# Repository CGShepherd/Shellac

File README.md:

# Project Shellac

Shellac is a controlled 78 rpm replay preamplifier design. `develop` is the working engineering authority; a tagged `main` release becomes production authority only after qualification and reproducibility gates close.

## Current authority

Read these first:

1. `config/decisions/current_decision_index.yaml`
2. `config/decisions/document_authority.yaml`
3. `docs/knowledge/DESIGN_PACK_INDEX.md`
4. current `generator/`, BOM and tests
5. current pre-SPICE assurance records in `docs/design_pack/`

Historical records are provenance and do not override later current authority.

## Live implementation versus selected-next architecture

- DR-037 complete RIAA: implemented.
- DR-038/SCH101: AE-071A gain programming remains live at approximately 14/18/22 dB; AE-075B selects LT5400BIMS8E-7#PBF and bonds EP9 to quiet 0VA. AE-076C selects two local per-channel passive cartridge-personality cards using SLW-102-01-G-D main sockets and TSW-102-07-G-D card headers; no card=BASE, with matched +47/+100 pF L/R service pairs. AE-076E-A qualifies the exact interface primitive; AE-076E-B implements H120/H220 in both generator and native PCB, removing the legacy ganged hardware. Three corrected project-local solid models pass KiCad STEP export; exact Samtec mated geometry remains open. RUN10 complete-stage tolerance/CMRR, personality-interface parasitics/matching, gain-shunt physical verification and bench qualification remain open.
- DR-039/SCH107: AE-074 migrates the AE-067 branch-local topology into the live generator: the retained 1 uF / 330 kOhm network exists only in each DIRECT/BYPASS branch, while the existing SCH107 high-pass branch provides intrinsic DC blocking. Native-PCB F8/net reconciliation is closed by AE-074; RUN09, RUN10, RUN12 and bench correlation remain open.
- SCH108/output interface: AE-075G implements exact Molex 5055780221 two-circuit PCB headers H801/H802 for the short rear-panel balanced-output looms, validates HOT/COLD native pad mapping with no 0VA conductor, corrects THAT1646 source semantics to 25 Ohm per leg / 50 Ohm differential, and passes the application-specific PRE90 2 kOhm load discriminator. H801/H802 XY remains provisional pending manual placement reconciliation; RUN06 load/cable stability and dynamic-THD bench gates remain open.
- AE-041 A1 + AE-075C hardware + AE-076B controls: exact NKK/C&K hardware remains frozen. AE-076B supersedes the AE-075D/E/F four-local-control-board/carrier-era ownership architecture with one main audio PCB carrying all seven controls directly; the upper cover, main PCB and controls form one removable service module. Six PCB-to-upper-cover supports are selected in principle, but exact support XY/Z, the C&K fit at the NKK-constrained control plane, control XY, footprints/courtyards, panel apertures and RUN10 parasitic acceptance remain B03-open. SR-040/AE-071B MH1-MH4 native geometry is retained only as interim physical CAD pending the AE-076B2 MCAD/digital-mock-up migration; no control inter-board harnesses are selected.
- SW905 mute: mechanical DPDT signal/0VA selection immediately before the THAT1646 drivers. No relay/timer/comparator architecture.

Do not change live circuitry merely to make it resemble a selected-next record. Migration requires a controlled qualification and implementation step.

## Power and grounding

AE-076A establishes +17.0 V / 0VA / -17.0 V as current Shellac regulated-rail authority and migrates the live generator, current simulation contract, commissioning expectations and native PCB rail identities together. Historical +/-18 V assurance evidence remains immutable provenance. AE-073's target-17 PSU discriminator remains supporting model evidence only: powered set-point, dropout, ripple, startup and thermal qualification remain open under RUN13/RUN14 and bench work. The selected direct 0VA-to-chassis population remains R909 = 0 Ohm fitted, with C909, D901 and D902 DNP. Shellac and Phoenix are independent designs.

## Simulation

AE-053 defines the LTspice/Python simulation architecture. AE-054 through AE-058 establish implemented toolchain and numerical-correlation evidence. The integrated full-system campaign remains governed by AE-048 and AE-050 with AE-049 retained as the historical numerical-acceptance basis; AE-076A establishes the current nominal +17 V / 0VA / -17 V rail condition and targeted rail/headroom evidence. AE-076D publishes the current qualification delta that maps the retained method to Grado Prestige 78C and BASE/+47/+100 differential personality states without relaxing criteria or claiming RUN08-RUN14 execution. Analytical Python is an independent live-state regression/correlation aid, not final integrated analogue authority.

## Basic validation

    python -m pytest -q
    python tools/audit_current_decision_index.py
    git diff --check

This repository is not yet a manufacturing baseline.

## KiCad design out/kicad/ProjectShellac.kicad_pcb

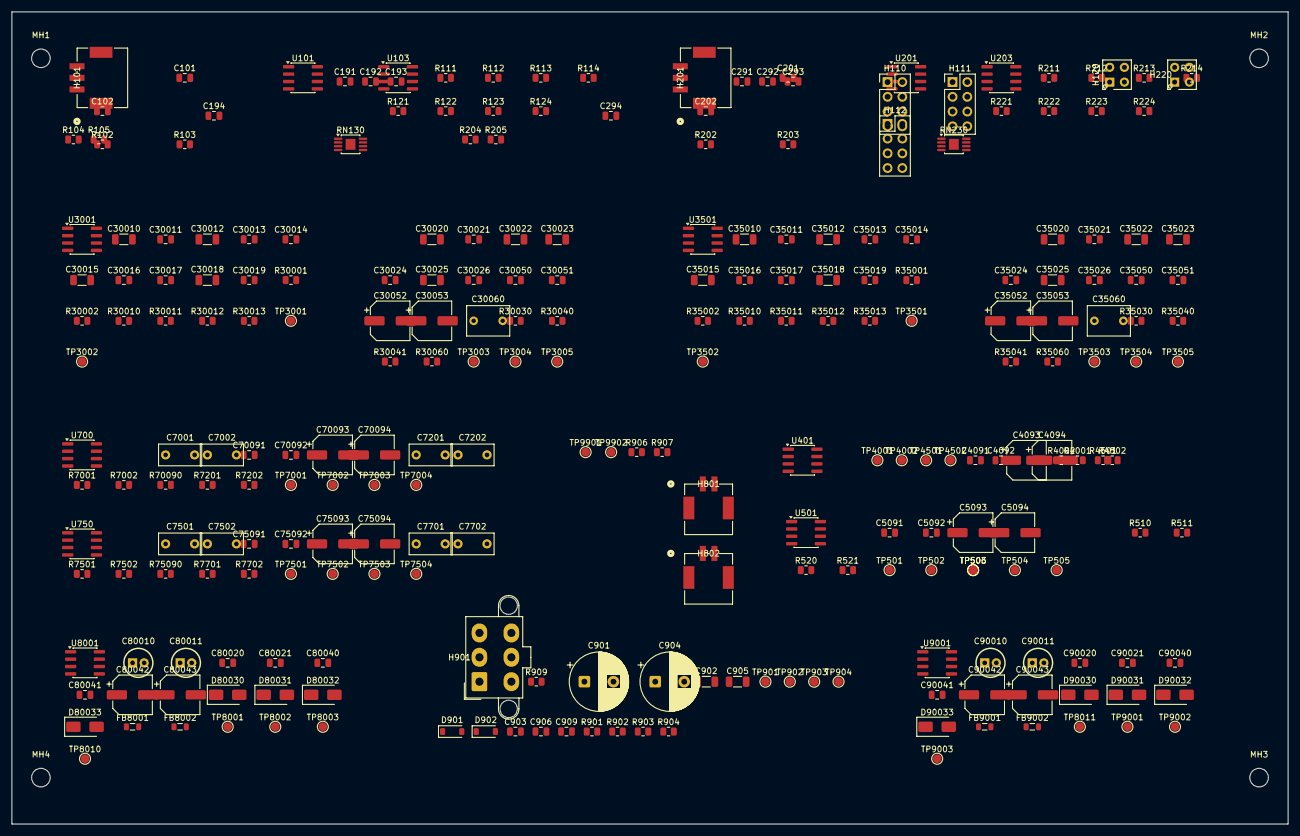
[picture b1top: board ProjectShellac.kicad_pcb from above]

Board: 4 copper layers, 220.0 x 140.0 mm, 256 parts (0 on the bottom side), 110 nets, no tracks yet.

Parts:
C101, C102, C201, C202: 47p; C_0805_2012Metric
C191, C192, C193, C194, C291, C292, C293, C294, C903, C906, C909, C4091, C4092, C5091, C5092, C30050, C30051, C35050, C35051, C70091, C70092, C75091, C75092, C80040, C80041, C90040, C90041: 100n; C_0805_2012Metric
C901, C904: 470u; CP_Radial_D10.0mm_P5.00mm
C902, C905: 1u; C_1206_3216Metric
C4093, C4094, C5093, C5094, C30052, C30053, C35052, C35053, C70093, C70094, C75093, C75094, C80042, C80043, C90042, C90043: 10u; CP_Elec_6.3x5.8
C7001, C7002, C7201, C7202, C7501, C7502, C7701, C7702: 470n; C_Rect_L7.2mm_W3.5mm_P5.00mm_FKS2_FKP2_MKS2_MKP2
C30010, C30012, C30015, C35010, C35012, C35015: 68n; C_1206_3216Metric
C30011, C35011: 5.6n; C_0805_2012Metric
C30013, C35013: 9.1n; C_0805_2012Metric
C30014, C35014: 560p; C_0805_2012Metric
C30016, C35016: 10n; C_0805_2012Metric
C30017, C35017: 470p; C_0805_2012Metric
C30018, C35018: 27n; C_1206_3216Metric
C30019, C35019: 2.4n; C_0805_2012Metric
C30020, C35020: 120n; C_1206_3216Metric
C30021, C35021: 12n; C_0805_2012Metric
C30022, C35022: 100n; C_1206_3216Metric
C30023, C35023: 56n; C_1206_3216Metric
C30024, C35024: 6.2n; C_0805_2012Metric
C30025, C35025: 33n; C_1206_3216Metric
C30026, C35026: 3.6n; C_0805_2012Metric
C30060, C35060: 1u; C_Rect_L7.2mm_W5.0mm_P5.00mm
C80010, C80011, C90010, C90011: 10u NP; Panasonic_ECEA1VN100U_D5.0mm_H11.0mm_P2.00mm
C80020, C80021, C90020, C90021: 100p; C_0805_2012Metric
D901, D902: DNP; D_SOD-123
D80030, D80031, D80032, D80033, D90030, D90031, D90032, D90033: S1G; D_SMA
FB8001, FB8002, FB9001, FB9002: Ferrite bead; L_0805_2012Metric
H101: L INPUT HARNESS; Molex_MicroLockPlus_5055780321_1x03_P2.00mm_Horizontal
H110: GAIN LOW 4-GANG; PinHeader_2x04_P2.54mm_Vertical
H111: GAIN HIGH 4-GANG; PinHeader_2x04_P2.54mm_Vertical
H112: GAIN DEFAULT / PARK; PinHeader_2x04_P2.54mm_Vertical
H120: L LOAD PERSONALITY; Samtec_SLW-102-01-G-D_2x02_P2.54mm_Vertical
H201: R INPUT HARNESS; Molex_MicroLockPlus_5055780321_1x03_P2.00mm_Horizontal
H220: R LOAD PERSONALITY; Samtec_SLW-102-01-G-D_2x02_P2.54mm_Vertical
H801: L OUTPUT HARNESS; Molex_MicroLockPlus_5055780221_1x02_P2.00mm_Horizontal
H802: R OUTPUT HARNESS; Molex_MicroLockPlus_5055780221_1x02_P2.00mm_Horizontal
H901: PCB DC HARNESS; Molex_Mini-Fit_Jr_5566-06A2_2x03_P4.20mm_Vertical
MH1, MH2, MH3, MH4: MountingHole_3.2mm_M3
R102, R103, R202, R203: 100R; R_0805_2012Metric
R104, R105, R204, R205: 23700; R_0805_2012Metric
R111, R121, R211, R221: 1000; R_0805_2012Metric
R112, R122, R212, R222: 999; R_0805_2012Metric
R113, R123, R213, R223: 332; R_0805_2012Metric
R114, R124, R214, R224: 866; R_0805_2012Metric
R510, R520: 2.2e+06; R_0805_2012Metric
R511, R521, R4001, R4501, R70090, R75090: 100; R_0805_2012Metric
R901, R902, R909: 0R; R_0805_2012Metric
R903, R904: 22k; R_0805_2012Metric
R906, R907, R30010, R30013, R35010, R35013: 8200; R_0805_2012Metric
R4002, R4502: 4700; R_0805_2012Metric
R7001, R7501: 20800; R_0805_2012Metric
R7002, R7502: 24300; R_0805_2012Metric
R7201, R7701: 8660; R_0805_2012Metric
R7202, R7702: 59000; R_0805_2012Metric
R30001, R35001: 100k; R_0805_2012Metric
R30002, R35002: 2.70k; R_0805_2012Metric
R30011, R35011: 2490; R_0805_2012Metric
R30012, R35012: 1430; R_0805_2012Metric
R30030, R35030: 750; R_0805_2012Metric
R30040, R35040: 10000; R_0805_2012Metric
R30041, R35041: 11000; R_0805_2012Metric
R30060, R35060: 330k; R_0805_2012Metric
RN130: L LT5400-7 1:4; MSOP-8-1EP_3x3mm_P0.65mm_EP1.68x1.88mm
RN230: R LT5400-7 1:4; MSOP-8-1EP_3x3mm_P0.65mm_EP1.68x1.88mm
TP501, TP8010: L_MODE_IN; TestPoint_Pad_D1.5mm
TP502, TP8011: R_MODE_IN; TestPoint_Pad_D1.5mm
TP503: MONO_AVG; TestPoint_Pad_D1.5mm
TP504: L_MODE_OUT; TestPoint_Pad_D1.5mm
TP505: R_MODE_OUT; TestPoint_Pad_D1.5mm
TP506: MONO_R_LEG; TestPoint_Pad_D1.5mm
TP901: +17VA_IN; TestPoint_Pad_D1.5mm
TP902: 0VA_IN; TestPoint_Pad_D1.5mm
TP903: -17VA_IN; TestPoint_Pad_D1.5mm
TP904: CHASSIS; TestPoint_Pad_D1.5mm
TP3001: L_EQ_IN; TestPoint_Pad_D1.5mm
TP3002: L_LF_EQ_OUT; TestPoint_Pad_D1.5mm
TP3003: L_HF_EQ_OUT; TestPoint_Pad_D1.5mm
TP3004: L_RECOVERY_OUT; TestPoint_Pad_D1.5mm
TP3005: L_POST_EQ; TestPoint_Pad_D1.5mm
TP3501: R_EQ_IN; TestPoint_Pad_D1.5mm
TP3502: R_LF_EQ_OUT; TestPoint_Pad_D1.5mm
TP3503: R_HF_EQ_OUT; TestPoint_Pad_D1.5mm
TP3504: R_RECOVERY_OUT; TestPoint_Pad_D1.5mm
TP3505: R_POST_EQ; TestPoint_Pad_D1.5mm
TP4001: L_BUFFER_IN; TestPoint_Pad_D1.5mm
TP4002: L_BUFFER_OUT; TestPoint_Pad_D1.5mm
TP4501: R_BUFFER_IN; TestPoint_Pad_D1.5mm
TP4502: R_BUFFER_OUT; TestPoint_Pad_D1.5mm
TP7001: L_RUMBLE_IN; TestPoint_Pad_D1.5mm
TP7002: L_HP1_OUT; TestPoint_Pad_D1.5mm
TP7003: L_HP2_OUT; TestPoint_Pad_D1.5mm
TP7004: L_RUMBLE_OUT; TestPoint_Pad_D1.5mm
TP7501: R_RUMBLE_IN; TestPoint_Pad_D1.5mm
TP7502: R_HP1_OUT; TestPoint_Pad_D1.5mm
TP7503: R_HP2_OUT; TestPoint_Pad_D1.5mm
TP7504: R_RUMBLE_OUT; TestPoint_Pad_D1.5mm
TP8001: L_DRIVER_IN; TestPoint_Pad_D1.5mm
TP8002: L_OUT_POS; TestPoint_Pad_D1.5mm
TP8003: L_OUT_NEG; TestPoint_Pad_D1.5mm
TP9001: R_DRIVER_IN; TestPoint_Pad_D1.5mm
TP9002: R_OUT_POS; TestPoint_Pad_D1.5mm
TP9003: R_OUT_NEG; TestPoint_Pad_D1.5mm
TP9901: +17V_LED_DRIVE; TestPoint_Pad_D1.5mm
TP9902: -17V_LED_DRIVE; TestPoint_Pad_D1.5mm
U101, U201, U401, U501, U700, U750: OPA1656; SOIC-8_3.9x4.9mm_P1.27mm
U103, U203: OPA1655; SOIC-8_3.9x4.9mm_P1.27mm
U3001, U3501: OPA1612; SOIC-8_3.9x4.9mm_P1.27mm
U8001: L THAT1646; SOIC-8_3.9x4.9mm_P1.27mm
U9001: R THAT1646; SOIC-8_3.9x4.9mm_P1.27mm

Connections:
0VA: C191.2, C192.1, C193.2, C194.1, C291.2, C292.1, C293.2, C294.1, C901.2, C902.2, C903.2, C904.1, C905.1, C906.1, C909.1, C4091.2, C4092.1, C4093.2, C4094.1, C5091.2, C5092.1, C5093.2, C5094.1, C30020.2, C30021.2, C30022.2, C30023.2, C30024.2, C30025.2, C30026.2, C30050.2, C30051.1, C30052.2, C30053.1, C35020.2, C35021.2, C35022.2, C35023.2, C35024.2, C35025.2, C35026.2, C35050.2, C35051.1, C35052.2, C35053.1, C70091.2, C70092.1, C70093.2, C70094.1, C75091.2, C75092.1, C75093.2, C75094.1, C80040.2, C80041.1, C80042.2, C80043.1, C90040.2, C90041.1, C90042.2, C90043.1, D901.1 (K), D902.2 (A), H111.2 (B1), H111.4 (B2), H111.6 (B3), H111.8 (B4), H901.1, R104.2, R105.1, R111.1, R121.1, R204.2, R205.1, R211.1, R221.1, R510.2, R520.2, R903.2, R904.1, R909.1, R7002.1, R7202.1, R7502.1, R7702.1, R30002.2, R30040.2, R30060.2, R35002.2, R35040.2, R35060.2, RN130.5, RN130.9 (EP), RN230.5, RN230.9 (EP), TP902.1 (TP), U8001.3 (GND), U9001.3 (GND)
+17V: C191.1, C193.1, C291.1, C293.1, C901.1, C902.1, C903.1, C4091.1, C4093.1, C5091.1, C5093.1, C30050.1, C30052.1, C35050.1, C35052.1, C70091.1, C70093.1, C75091.1, C75093.1, C80040.1, C80042.1, C90040.1, C90042.1, D80030.1 (K), D80032.1 (K), D90030.1 (K), D90032.1 (K), R901.2, R903.1, R906.2, U101.8 (+V), U103.7 (+V), U201.8 (+V), U203.7 (+V), U401.8 (+V), U501.8 (+V), U700.8 (+V), U750.8 (+V), U3001.8 (+V), U3501.8 (+V), U8001.6 (+V), U9001.6 (+V)
-17V: C192.2, C194.2, C292.2, C294.2, C904.2, C905.2, C906.2, C4092.2, C4094.2, C5092.2, C5094.2, C30051.2, C30053.2, C35051.2, C35053.2, C70092.2, C70094.2, C75092.2, C75094.2, C80041.2, C80043.2, C90041.2, C90043.2, D80031.2 (A), D80033.2 (A), D90031.2 (A), D90033.2 (A), R902.2, R904.2, R907.2, U101.4 (-V), U103.4 (-V), U201.4 (-V), U203.4 (-V), U401.4 (-V), U501.4 (-V), U700.4 (-V), U750.4 (-V), U3001.4 (-V), U3501.4 (-V), U8001.5 (-V), U9001.5 (-V)
/INPUT_L_NEG: H101.3, R103.1
/INPUT_L_POS: H101.2, R102.1
/INPUT_R_NEG: H201.3, R203.1
/INPUT_R_POS: H201.2, R202.1
/OUTPUT_L_NEG: C80021.1, D80032.2 (A), D80033.1 (K), FB8002.2, H801.2, TP8003.1 (TP)
/OUTPUT_L_POS: C80020.2, D80030.2 (A), D80031.1 (K), FB8001.2, H801.1, TP8002.1 (TP)
/OUTPUT_R_NEG: C90021.1, D90032.2 (A), D90033.1 (K), FB9002.2, H802.2, TP9003.1 (TP)
/OUTPUT_R_POS: C90020.2, D90030.2 (A), D90031.1 (K), FB9001.2, H802.1, TP9002.1 (TP)
/SCH101 Balanced Input and Differential Conversion/SCH101_L_LOAD_NEG: C102.2, H120.2 (NEG_A), H120.3 (NEG_B), R103.2, R105.2, U101.5 (IN+)
/SCH101 Balanced Input and Differential Conversion/SCH101_L_LOAD_POS: C101.1, H120.1 (POS_A), H120.4 (POS_B), R102.2, R104.1, U101.3 (IN+)
/SCH101 Balanced Input and Differential Conversion/SCH101_L_LT5400_MINUS_SRC: R122.2, R123.1, RN130.2, U101.7 (OUT)
/SCH101 Balanced Input and Differential Conversion/SCH101_L_LT5400_MINUS_SUM: RN130.1, RN130.7, U103.2 (IN-)
/SCH101 Balanced Input and Differential Conversion/SCH101_L_LT5400_PLUS_SRC: R112.2, R113.1, RN130.3, U101.1 (OUT)
/SCH101 Balanced Input and Differential Conversion/SCH101_L_LT5400_PLUS_SUM: RN130.4, RN130.6, U103.3 (IN+)
/SCH101 Balanced Input and Differential Conversion/SCH101_L_MINUS_FB: H110.4 (B2), R121.2, R122.1, R124.1, U101.6 (FB-)
/SCH101 Balanced Input and Differential Conversion/SCH101_L_MINUS_HIGH_BRANCH: H111.3 (A2), R124.2
/SCH101 Balanced Input and Differential Conversion/SCH101_L_MINUS_LOW_BRANCH: H110.3 (A2), R123.2
/SCH101 Balanced Input and Differential Conversion/SCH101_L_PLUS_FB: H110.2 (B1), R111.2, R112.1, R114.1, U101.2 (FB-)
/SCH101 Balanced Input and Differential Conversion/SCH101_L_PLUS_HIGH_BRANCH: H111.1 (A1), R114.2
/SCH101 Balanced Input and Differential Conversion/SCH101_L_PLUS_LOW_BRANCH: H110.1 (A1), R113.2
/SCH101 Balanced Input and Differential Conversion/SCH101_R_LOAD_NEG: C202.2, H220.2 (NEG_A), H220.3 (NEG_B), R203.2, R205.2, U201.5 (IN+)
/SCH101 Balanced Input and Differential Conversion/SCH101_R_LOAD_POS: C201.1, H220.1 (POS_A), H220.4 (POS_B), R202.2, R204.1, U201.3 (IN+)
/SCH101 Balanced Input and Differential Conversion/SCH101_R_LT5400_MINUS_SRC: R222.2, R223.1, RN230.2, U201.7 (OUT)
/SCH101 Balanced Input and Differential Conversion/SCH101_R_LT5400_MINUS_SUM: RN230.1, RN230.7, U203.2 (IN-)
/SCH101 Balanced Input and Differential Conversion/SCH101_R_LT5400_PLUS_SRC: R212.2, R213.1, RN230.3, U201.1 (OUT)
/SCH101 Balanced Input and Differential Conversion/SCH101_R_LT5400_PLUS_SUM: RN230.4, RN230.6, U203.3 (IN+)
/SCH101 Balanced Input and Differential Conversion/SCH101_R_MINUS_FB: H110.8 (B4), R221.2, R222.1, R224.1, U201.6 (FB-)
/SCH101 Balanced Input and Differential Conversion/SCH101_R_MINUS_HIGH_BRANCH: H111.7 (A4), R224.2
/SCH101 Balanced Input and Differential Conversion/SCH101_R_MINUS_LOW_BRANCH: H110.7 (A4), R223.2
/SCH101 Balanced Input and Differential Conversion/SCH101_R_PLUS_FB: H110.6 (B3), R211.2, R212.1, R214.1, U201.2 (FB-)
/SCH101 Balanced Input and Differential Conversion/SCH101_R_PLUS_HIGH_BRANCH: H111.5 (A3), R214.2
/SCH101 Balanced Input and Differential Conversion/SCH101_R_PLUS_LOW_BRANCH: H110.5 (A3), R213.2
/SCH106 Audio-Box Power Entry and Ground Bond/+17VA_IN: H901.2, R901.1, TP901.1 (TP)
/SCH106 Audio-Box Power Entry and Ground Bond/-17VA_IN: H901.3, R902.1, TP903.1 (TP)
CHASSIS: C101.2, C102.1, C201.2, C202.1, C909.2, C80020.1, C80021.2, C90020.1, C90021.2, D901.2 (A), D902.1 (K), H101.1, H201.1, H901.4, R909.2, TP904.1 (TP)
unnamed: C7001.1, C7002.2, R7001.1
unnamed: C7201.1, C7202.2, R7201.1
unnamed: C7501.1, C7502.2, R7501.1
unnamed: C7701.1, C7702.2, R7701.1
unnamed: C30010.1, C30011.1, R30010.2
unnamed: C30010.2, C30011.2
unnamed: C30012.1, C30013.1, C30014.1, R30011.2
unnamed: C30012.2, C30013.2, C30014.2
unnamed: C30015.1, C30016.1, C30017.1, R30012.2
unnamed: C30015.2, C30016.2, C30017.2
unnamed: C30018.1, C30019.1, R30013.2
unnamed: C30018.2, C30019.2
unnamed: C30020.1, C30021.1
unnamed: C30023.1, C30024.1
unnamed: C30025.1, C30026.1
unnamed: C30060.1, R30060.1
unnamed: C35010.1, C35011.1, R35010.2
unnamed: C35010.2, C35011.2
unnamed: C35012.1, C35013.1, C35014.1, R35011.2
unnamed: C35012.2, C35013.2, C35014.2
unnamed: C35015.1, C35016.1, C35017.1, R35012.2
unnamed: C35015.2, C35016.2, C35017.2
unnamed: C35018.1, C35019.1, R35013.2
unnamed: C35018.2, C35019.2
unnamed: C35020.1, C35021.1
unnamed: C35023.1, C35024.1
unnamed: C35025.1, C35026.1
unnamed: C35060.1, R35060.1
unnamed: R30001.1, R30010.1, R30011.1, R30012.1, R30013.1, R30030.1, TP3002.1 (TP), U3001.1 (OUT)
unnamed: R30030.2, TP3003.1 (TP), U3001.5 (IN+)
unnamed: R35001.1, R35010.1, R35011.1, R35012.1, R35013.1, R35030.1, TP3502.1 (TP), U3501.1 (OUT)
unnamed: R35030.2, TP3503.1 (TP), U3501.5 (IN+)
unnamed: C7201.2, R7001.2, TP7002.1 (TP), U700.1 (OUT), U700.2 (IN-)
unnamed: R7201.2, R70090.1, TP7003.1 (TP), U700.6 (IN-), U700.7 (OUT)
unnamed: C7701.2, R7501.2, TP7502.1 (TP), U750.1 (OUT), U750.2 (IN-)
unnamed: R7701.2, R75090.1, TP7503.1 (TP), U750.6 (IN-), U750.7 (OUT)
unnamed: TP8001.1 (TP), U8001.4 (IN)
unnamed: TP9001.1 (TP), U9001.4 (IN)
unnamed: R906.1, TP9901.1 (TP)
unnamed: R907.1, TP9902.1 (TP)
unnamed: R4001.1, U401.1 (OUT), U401.2 (IN-)
unnamed: R4501.1, U401.6 (IN-), U401.7 (OUT)
unnamed: R510.1, U501.3 (IN)
unnamed: R511.1, U501.1 (OUT), U501.2 (IN-)
unnamed: R520.1, U501.5 (IN)
unnamed: R521.1, U501.6 (IN-), U501.7 (OUT)
unnamed: C7002.1, R7002.2, U700.3 (IN)
unnamed: C7202.1, R7202.2, U700.5 (IN)
unnamed: C7502.1, R7502.2, U750.3 (IN)
unnamed: C7702.1, R7702.2, U750.5 (IN)
unnamed: R30001.2, R30002.1, U3001.2 (FB-)
unnamed: R30040.1, R30041.2, U3001.6 (FB-)
unnamed: R35001.2, R35002.1, U3501.2 (FB-)
unnamed: R35040.1, R35041.2, U3501.6 (FB-)
unnamed: C80010.1, FB8001.1, U8001.8 (OUT+)
unnamed: C80011.1, FB8002.1, U8001.1 (OUT-)
unnamed: C80010.2, U8001.7 (SNS+)
unnamed: C80011.2, U8001.2 (SNS-)
unnamed: C90010.1, FB9001.1, U9001.8 (OUT+)
unnamed: C90011.1, FB9002.1, U9001.1 (OUT-)
unnamed: C90010.2, U9001.7 (SNS+)
unnamed: C90011.2, U9001.2 (SNS-)
ROOT__BUFFERED_L: R4001.2, TP501.1 (TP), TP4002.1 (TP)
ROOT__BUFFERED_R: R4501.2, TP502.1 (TP), TP4502.1 (TP)
ROOT__FILTERED_L: TP4001.1 (TP), TP7004.1 (TP), U401.3 (IN)
ROOT__FILTERED_R: TP4501.1 (TP), TP7504.1 (TP), U401.5 (IN)
ROOT__MODE_L: R511.2, TP504.1 (TP), TP8010.1 (TP)
ROOT__MODE_R: R521.2, TP505.1 (TP), TP8011.1 (TP)
ROOT__POST_EQ_L: C7001.2, C30060.2, R30041.1, TP3004.1 (TP), TP3005.1 (TP), TP7001.1 (TP), U3001.7 (OUT)
ROOT__POST_EQ_R: C7501.2, C35060.2, R35041.1, TP3504.1 (TP), TP3505.1 (TP), TP7501.1 (TP), U3501.7 (OUT)
ROOT__PRE_EQ_L: RN130.8, TP3001.1 (TP), U103.6 (OUT), U3001.3 (IN+)
ROOT__PRE_EQ_R: RN230.8, TP3501.1 (TP), U203.6 (OUT), U3501.3 (IN+)
